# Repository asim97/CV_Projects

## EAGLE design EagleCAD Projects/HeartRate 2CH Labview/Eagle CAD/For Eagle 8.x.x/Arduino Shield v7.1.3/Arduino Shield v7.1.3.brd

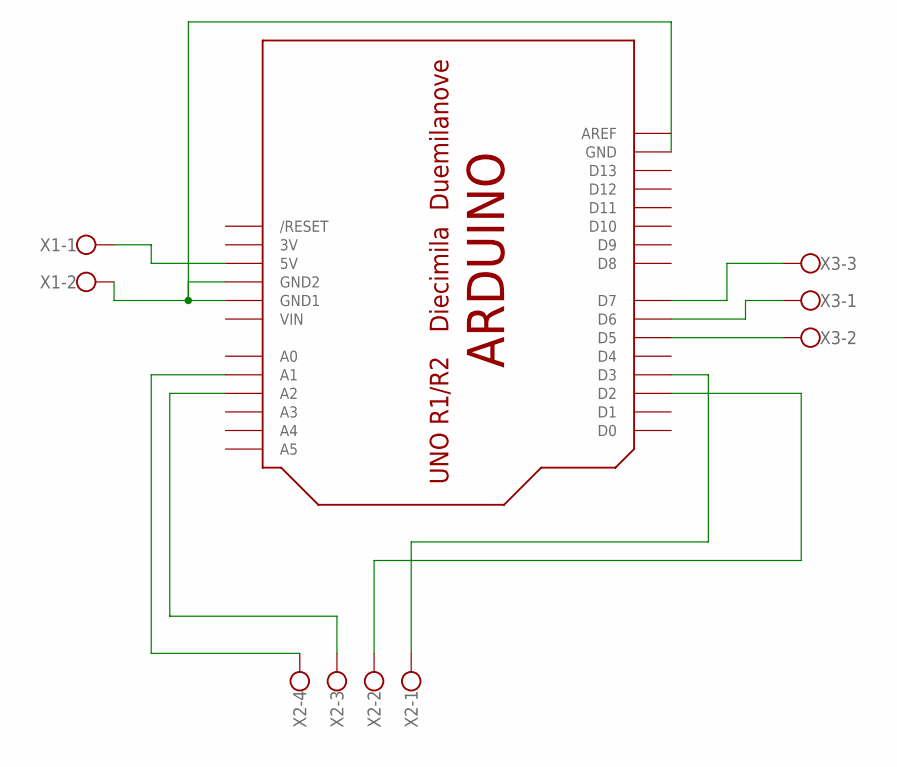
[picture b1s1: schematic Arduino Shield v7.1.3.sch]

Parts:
U$1: ARDUINOUNO; ARDUINO
X1: W237-102
X2: W237-4
X3: W237-103

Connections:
3V: U$1.3V
GND: U$1.GND, U$1.GND1, U$1.GND2, X1.2
unnamed: U$1.A1, X2.4
unnamed: U$1.A2, X2.3
unnamed: U$1.D3, X2.1
unnamed: U$1.D5, X3.2
unnamed: U$1.D6, X3.1
unnamed: U$1.D7, X3.3
unnamed: U$1.D2, X2.2
unnamed: U$1.5V, X1.1
VIN: U$1.VIN

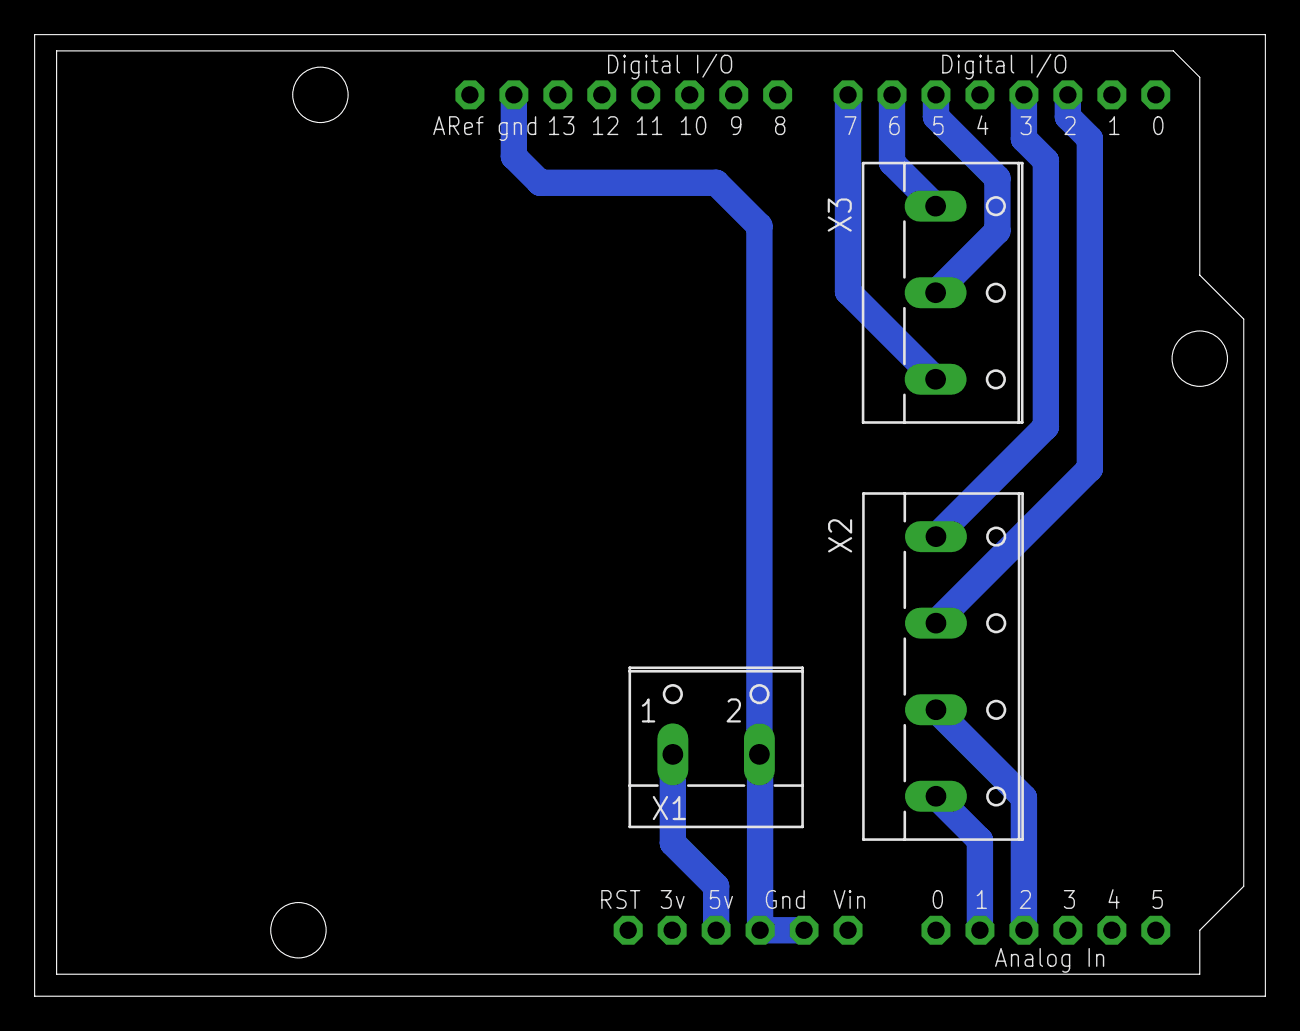
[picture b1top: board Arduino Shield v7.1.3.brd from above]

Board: 2 copper layers, 71.1 x 55.6 mm, 4 parts (0 on the bottom side), 9 nets.

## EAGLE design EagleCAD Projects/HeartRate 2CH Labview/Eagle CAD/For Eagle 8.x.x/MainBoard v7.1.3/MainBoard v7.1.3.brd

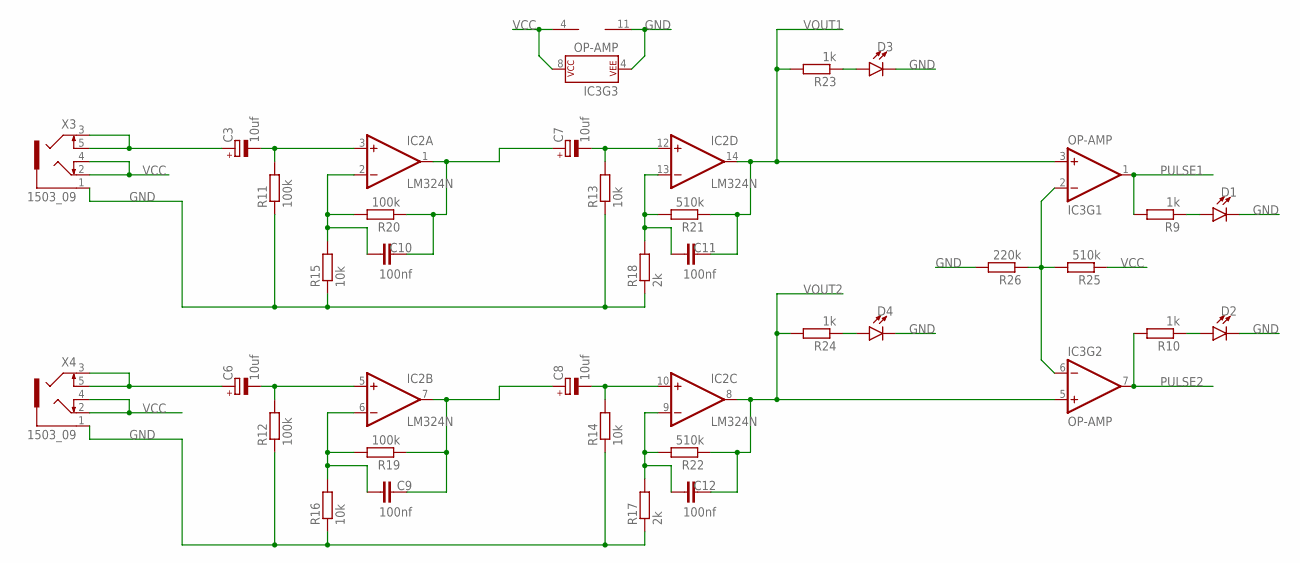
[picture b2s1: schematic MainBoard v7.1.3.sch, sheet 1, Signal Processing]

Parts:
C3, C6, C7, C8: 10uf; E2-5
C9, C10, C11, C12: 100nf; C050-030X075
D1, D2, D3, D4: LED5MM; LED_5MM
IC2: LM324N; DIL14
IC3: OP-AMP; DIP08
R9, R10, R23, R24: 1k; 0207/10
R11, R12, R19, R20: 100k; 0207/10
R13, R14, R15, R16: 10k; 0207/10
R17, R18: 2k; 0207/10
R21, R22, R25: 510k; 0207/10
R26: 220k; 0207/10
X3, X4: 1503_09

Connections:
GND: D1.K (C), D2.K (C), D3.K (C), D4.K (C), IC2.11 (V-), IC3.4 (P$V-), R11.1, R12.1, R13.1, R14.1, R15.1, R16.1, R17.1, R18.1, R26.2, X3.1, X4.1; also elsewhere on the board
unnamed: C8.+, C9.2, IC2.7 (OUT), R19.1
unnamed: C9.1, IC2.6 (-IN), R16.2, R19.2
unnamed: D1.A, R9.1
unnamed: C7.+, C10.2, IC2.1 (OUT), R20.1
unnamed: C10.1, IC2.2 (-IN), R15.2, R20.2
unnamed: C11.1, IC2.13 (-IN), R18.2, R21.2
unnamed: IC3.2 (-IN), IC3.6 (-IN), R25.2, R26.1
unnamed: C12.1, IC2.9 (-IN), R17.2, R22.2
unnamed: C6.+, X4.3, X4.5
unnamed: D2.A, R10.1
unnamed: C3.+, X3.3, X3.5
unnamed: C6.-, IC2.5 (+IN), R12.2
unnamed: C7.-, IC2.12 (+IN), R13.2
unnamed: C8.-, IC2.10 (+IN), R14.2
unnamed: C3.-, IC2.3 (+IN), R11.2
unnamed: D3.A, R23.1
unnamed: D4.A, R24.1
PULSE1: IC3.1 (OUT), R9.2; also elsewhere on the board
PULSE2: IC3.7 (OUT), R10.2; also elsewhere on the board
VCC: IC2.4 (V+), IC3.8 (P$V+), R25.1, X3.2, X3.4, X4.2, X4.4; also elsewhere on the board
VOUT1: C11.2, IC2.14 (OUT), IC3.3 (+IN), R21.1, R23.2; also elsewhere on the board
VOUT2: C12.2, IC2.8 (OUT), IC3.5 (+IN), R22.1, R24.2; also elsewhere on the board

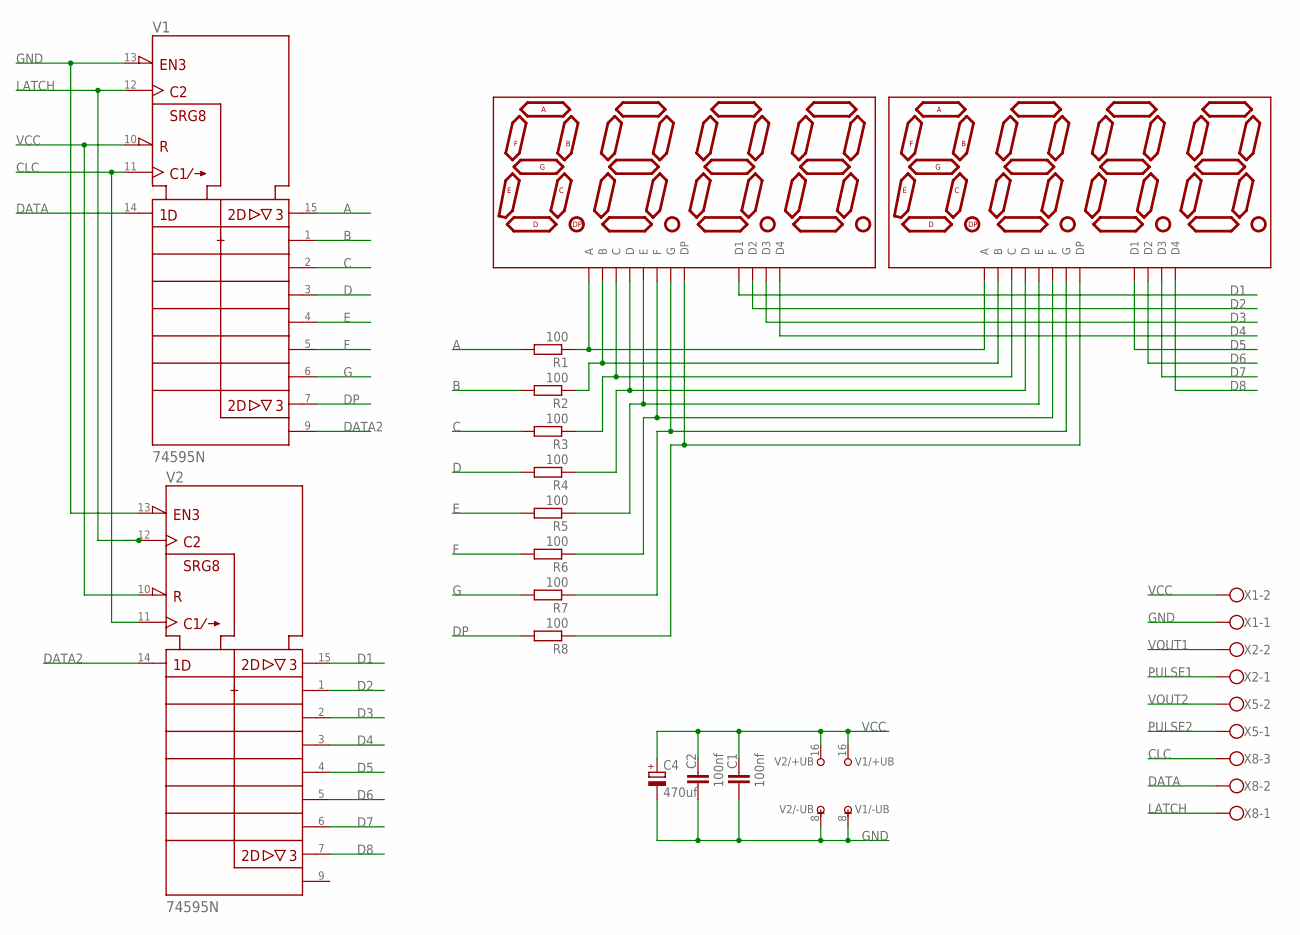
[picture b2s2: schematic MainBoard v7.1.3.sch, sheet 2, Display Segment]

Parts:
C1, C2: 100nf; C050-030X075
C4: 470uf; E3,5-8
DISP1, DISP2: ATA8041AB; 7-SEGMENT-4DIGIT-20MM
R1, R2, R3, R4, R5, R6, R7, R8: 100; 0207/10
V1, V2: 74595N; DIL16
X1, X2, X5: W237-102
X8: W237-103

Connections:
A: R1.2, V1.15 (QA)
B: R2.2, V1.1 (QB)
C: R3.2, V1.2 (QC)
CLC: V1.11 (SRCK), V2.11 (SRCK), X8.3
D: R4.2, V1.3 (QD)
D1: DISP2.12 (D1), V2.15 (QA)
D2: DISP2.9 (D2), V2.1 (QB)
D3: DISP2.8 (D3), V2.2 (QC)
D4: DISP2.6 (D4), V2.3 (QD)
D5: DISP1.12 (D1), V2.4 (QE)
D6: DISP1.9 (D2), V2.5 (QF)
D7: DISP1.8 (D3), V2.6 (QG)
D8: DISP1.6 (D4), V2.7 (QH)
DATA: V1.14 (SER), X8.2
DATA2: V1.9 (QH*), V2.14 (SER)
DP: R8.2, V1.7 (QH)
E: R5.2, V1.4 (QE)
F: R6.2, V1.5 (QF)
G: R7.2, V1.6 (QG)
GND: C1.1, C2.1, C4.-, V1.8 (-UB), V1.13 (!G), V2.8 (-UB), V2.13 (!G), X1.1; also elsewhere on the board
LATCH: V1.12 (RCK), V2.12 (RCK), X8.1
unnamed: DISP1.11 (A), DISP2.11 (A), R1.1
unnamed: DISP1.7 (B), DISP2.7 (B), R2.1
unnamed: DISP1.4 (C), DISP2.4 (C), R3.1
unnamed: DISP1.2 (D), DISP2.2 (D), R4.1
unnamed: DISP1.1 (E), DISP2.1 (E), R5.1
unnamed: DISP1.10 (F), DISP2.10 (F), R6.1
unnamed: DISP1.5 (G), DISP2.5 (G), R7.1
unnamed: DISP1.3 (DP), DISP2.3 (DP), R8.1
PULSE1: X2.1; also elsewhere on the board
PULSE2: X5.1; also elsewhere on the board
VCC: C1.2, C2.2, C4.+, V1.10 (!SRCLR), V1.16 (+UB), V2.10 (!SRCLR), V2.16 (+UB), X1.2; also elsewhere on the board
VOUT1: X2.2; also elsewhere on the board
VOUT2: X5.2; also elsewhere on the board

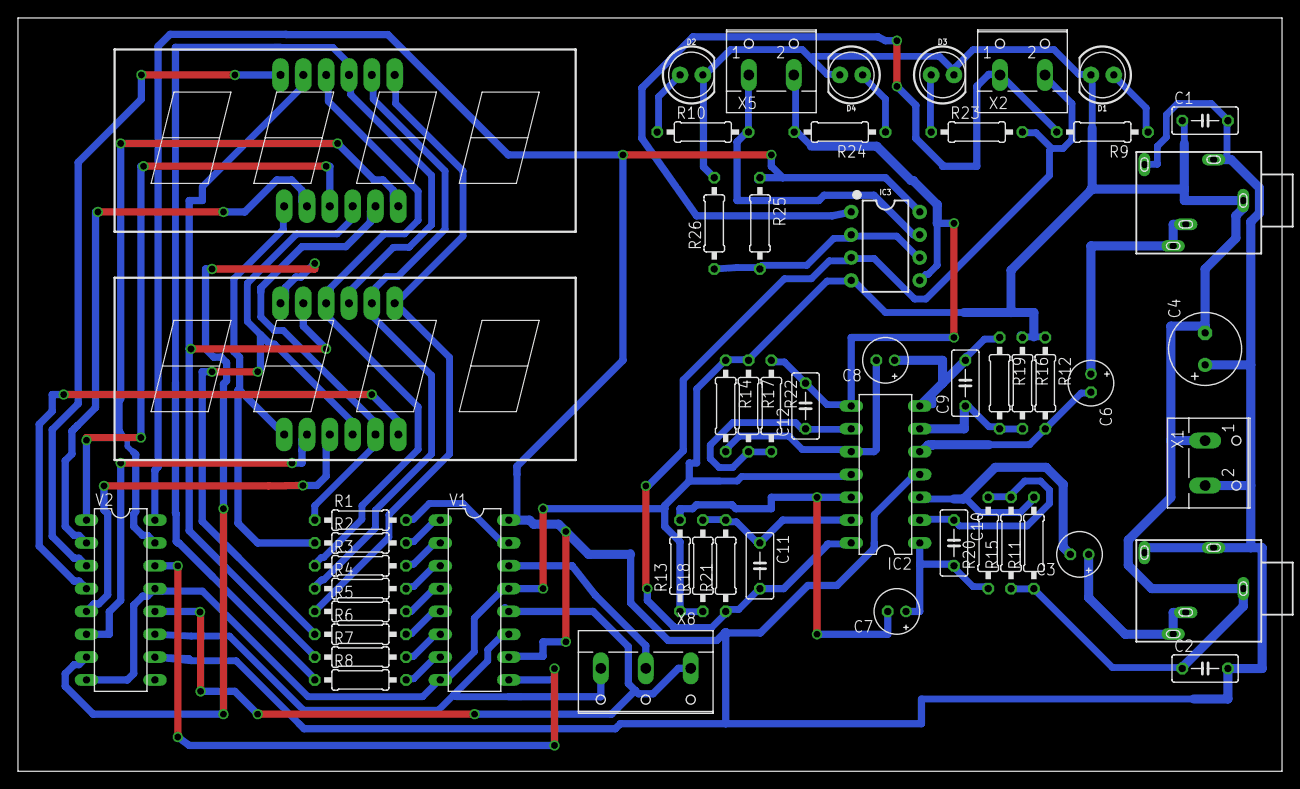
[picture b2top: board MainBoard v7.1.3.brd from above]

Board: 2 copper layers, 140.6 x 83.8 mm, 53 parts (0 on the bottom side), 51 nets.

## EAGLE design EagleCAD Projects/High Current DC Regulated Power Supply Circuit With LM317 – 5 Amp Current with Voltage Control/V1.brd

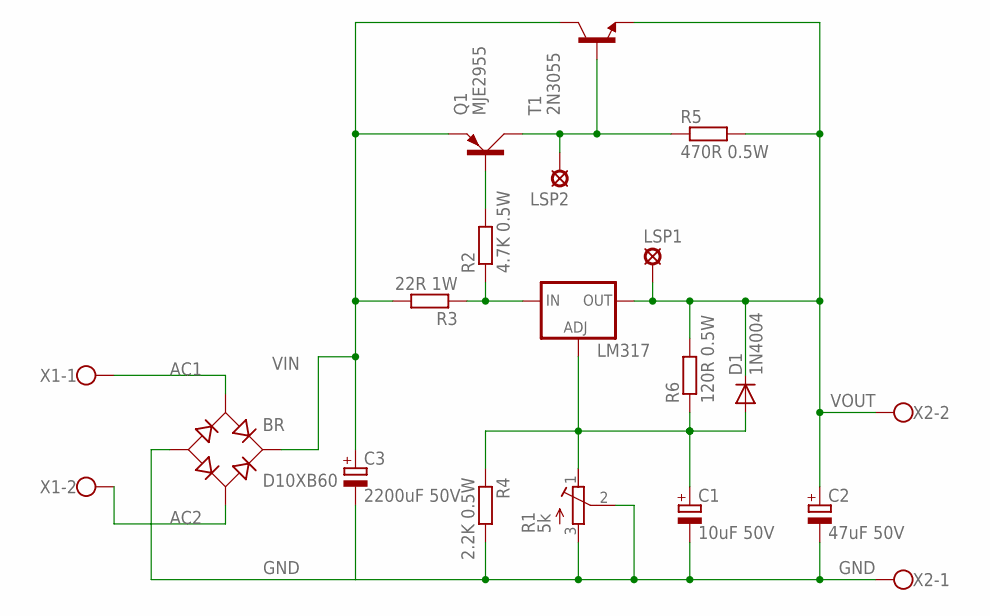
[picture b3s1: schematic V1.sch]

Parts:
BR: D10XB60; DX10B60
C1: 10uF 50V; E2,5-5
C2: 47uF 50V; E5-8,5
C3: 2200uF 50V; E7,5-18
D1: 1N4004; DO41-10
LM317: V_REG_317SINK; TO220-ADJ
LSP1, LSP2: SE13
Q1: MJE2955; TO220AV
R1: 5k; RTRIMT93XA
R2: 4.7K 0.5W; 0617/17
R3: 22R 1W; 0617/17
R4: 2.2K 0.5W; 0617/17
R5: 470R 0.5W; 0617/17
R6: 120R 0.5W; 0617/17
T1: 2N3055; TO3
X1, X2: W237-102

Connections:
AC1: BR.AC1, X1.1
AC2: BR.AC2, X1.2
GND: BR.-, C1.-, C2.-, C3.-, R1.2 (S), R1.3 (A), R4.2, X2.1
unnamed: LM317.IN, R2.1, R3.1
unnamed: Q1.B, R2.2
unnamed: LSP2.MP, Q1.C, R5.1, T1.B
unnamed: C1.+, D1.A, LM317.ADJ, R1.1 (E), R4.1, R6.1
VIN: BR.+, C3.+, Q1.E, R3.2, T1.C, T1.C/ (C)
VOUT: C2.+, D1.C, LM317.OUT, LSP1.MP, R5.2, R6.2, T1.E, X2.2

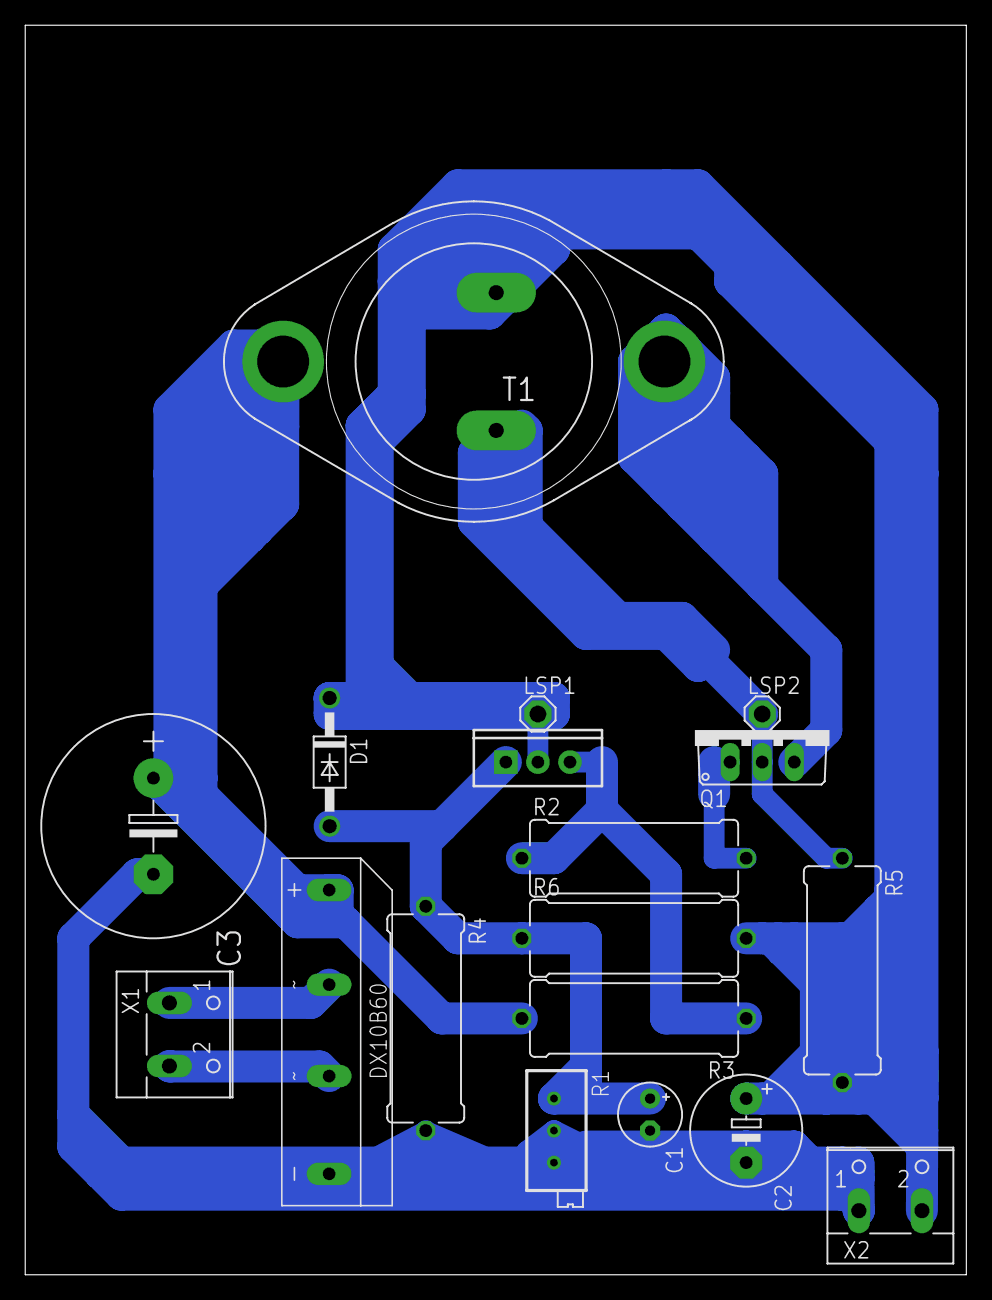
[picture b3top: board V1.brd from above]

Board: 2 copper layers, 74.6 x 99.0 mm, 18 parts (0 on the bottom side), 9 nets.

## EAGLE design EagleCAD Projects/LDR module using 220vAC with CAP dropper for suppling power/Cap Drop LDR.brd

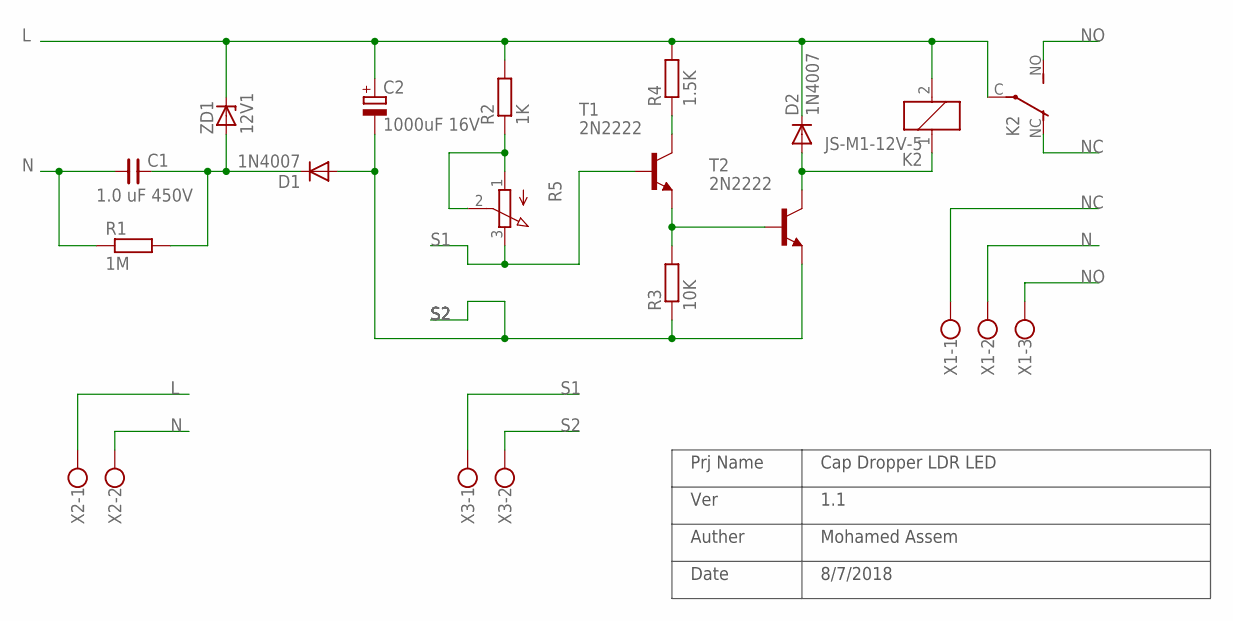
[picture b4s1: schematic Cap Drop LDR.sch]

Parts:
C1: 1.0 uF 450V; C150-190X070
C2: 1000uF 16V; E5-8,5
D1, D2: 1N4007; DO41-10
K2: JS-M1-12V-5; JS-M
R1: 1M; 0207/10
R2: 1K; 0207/10
R3: 10K; 0207/10
R4: 1.5K; 0207/10
R5: 3RP/1610N
T1, T2: 2N2222; TO92-EBC-OVAL
X1: W237-103
X2, X3: W237-102
ZD1: 12V1; DO35Z10

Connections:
L: C2.+, D2.C, K2.2, K2.C, R2.2, R4.2, X2.1, ZD1.C
N: C1.1, R1.1, X1.2, X2.2
unnamed: R3.2, T1.E, T2.B
unnamed: D2.A, K2.1, T2.C
unnamed: C1.2, D1.C, R1.2, ZD1.A
unnamed: R4.1, T1.C
unnamed: R2.1, R5.1 (A), R5.2 (S)
NC: K2.NC (O), X1.1
NO: K2.NO (S), X1.3
S1: R5.3 (E), T1.B, X3.1
S2: C2.-, D1.A, R3.1, T2.E, X3.2

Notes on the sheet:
Prj Name
Ver
Auther
Date
Cap Dropper LDR LED
Mohamed Assem
8/7/2018
1.1

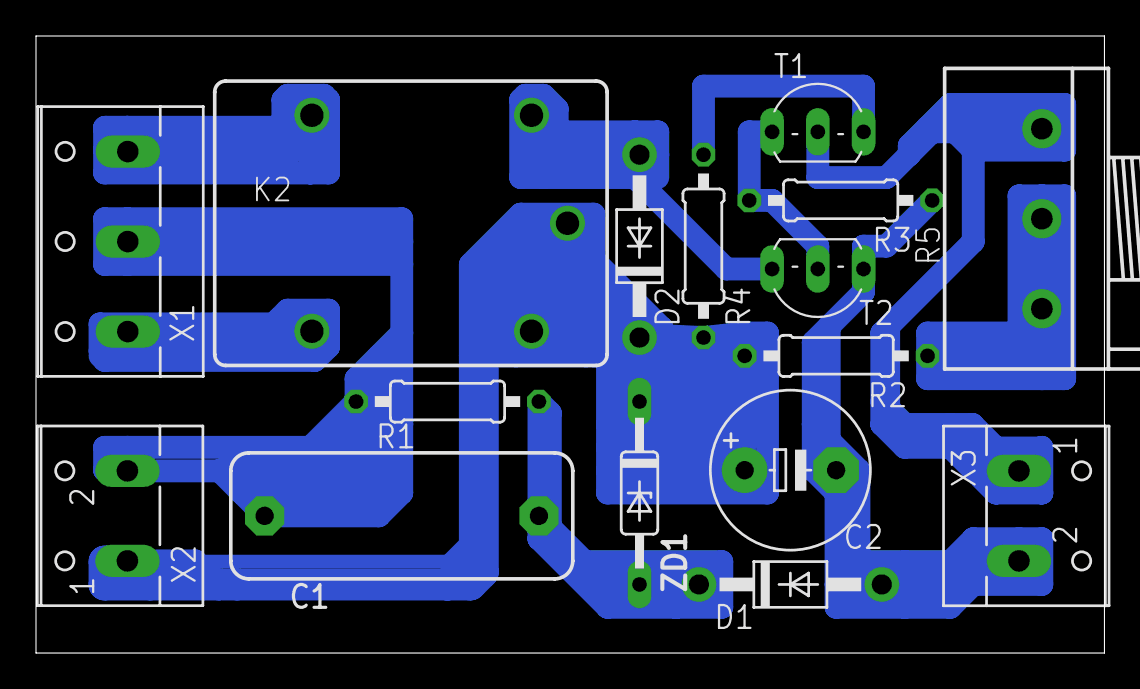
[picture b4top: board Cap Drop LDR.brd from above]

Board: 2 copper layers, 59.4 x 34.3 mm, 16 parts (0 on the bottom side), 11 nets.

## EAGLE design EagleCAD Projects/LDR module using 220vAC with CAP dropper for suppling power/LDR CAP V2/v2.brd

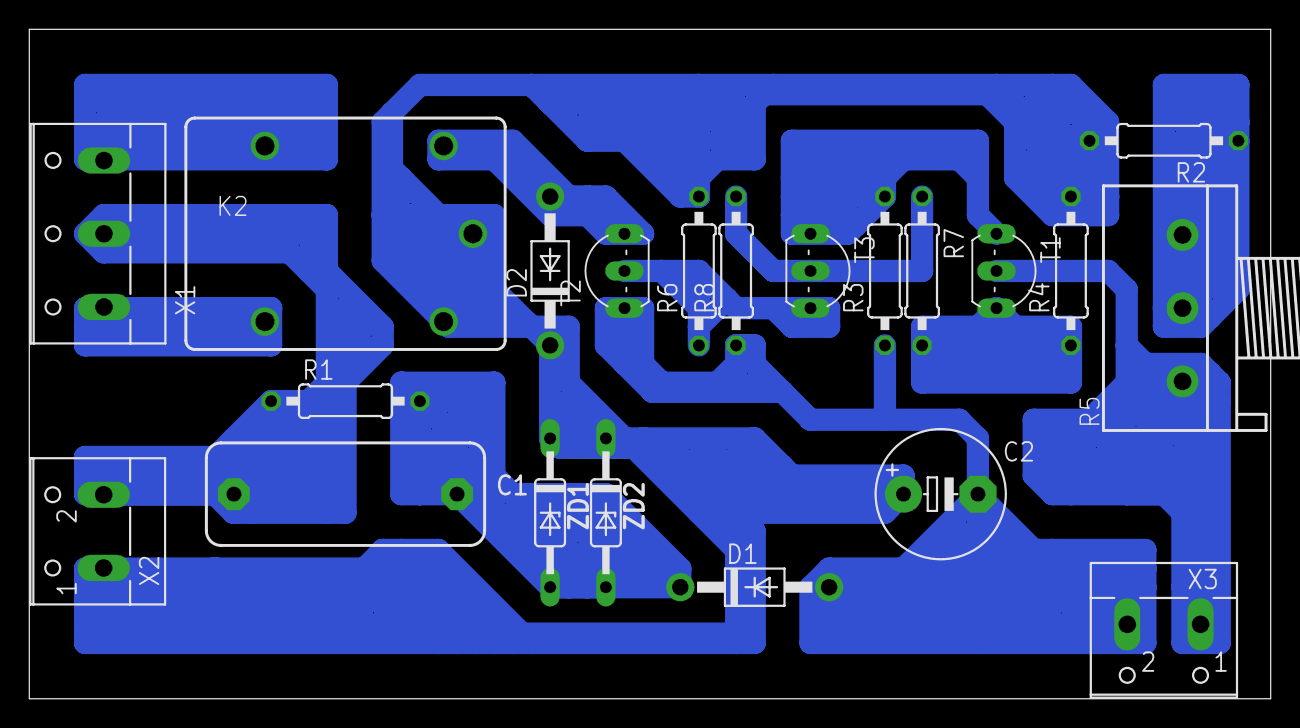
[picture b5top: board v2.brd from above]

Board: 2 copper layers, 84.8 x 45.7 mm, 21 parts (0 on the bottom side), 13 nets.

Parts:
C1: 1 uF 450V; C150-190X070
C2: 1000uF 35V; E5-8,5
D1, D2: 1N4007; DO41-10
K2: JS-M1-24V-5; JS-M
R1: 1M; 0207/10
R2, R6: 1K; 0207/10
R3: 51K; 0207/10
R4: 10K; 0207/10
R5: 100k; 3RP/1610N
R7, R8: 22K; 0207/10
T1, T2, T3: 2N2222; TO92-EBC-OVAL
X1: W237-103
X2, X3: W237-102
ZD1, ZD2: 24V 1Wat; DO35Z10

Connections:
L: C2.+, D2.C, K2.2, K2.C, R2.2, R4.2, R6.2, X2.1, ZD1.C, ZD2.C
N: C1.1, R1.1, X1.2, X2.2
unnamed: R7.1, R8.2, T3.B
unnamed: R3.2, T1.E, T3.E
unnamed: D2.A, K2.1, T2.C
unnamed: C1.2, D1.C, R1.2, ZD1.A, ZD2.A
unnamed: R4.1, R7.2, T1.C
unnamed: R6.1, T2.B, T3.C
unnamed: R2.1, R5.2, R5.3
NC: K2.NC, X1.1
NO: K2.NO, X1.3
S1: R5.1, T1.B, X3.1
S2: C2.-, D1.A, R3.1, R8.1, T2.E, X3.2

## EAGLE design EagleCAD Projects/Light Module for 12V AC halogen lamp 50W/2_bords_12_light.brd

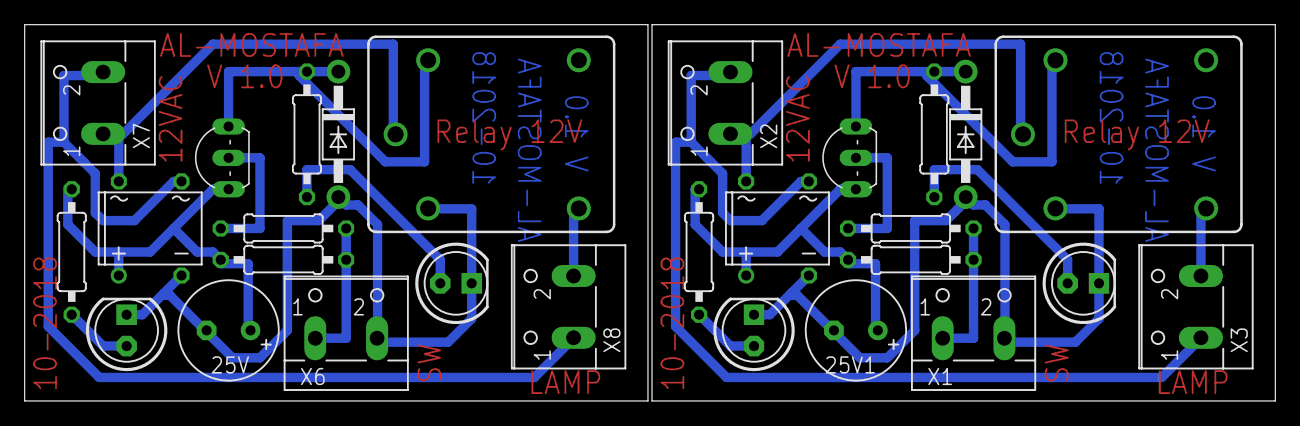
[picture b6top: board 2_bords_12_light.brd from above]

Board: 2 copper layers, 101.3 x 30.5 mm, 28 parts (0 on the bottom side), 20 nets.

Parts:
25V, 25V1: 100uF; E3,5-8
B1, B2: DBDB101G; DB
D1, D2: 1N5817; DO41-10
K1, K3: JS-M1-24V-5; JS-M
LD1, LD2, LD3, LD4: LED5MM
R1, R3: 2.2k; 0207/10
R2, R4: 10K; 0207/10
R5, R6, R7, R8: 10k; 0207/10
T1, T3: 2N5401; TO92-EBC
X1, X2, X3, X6, X7, X8: W237-102

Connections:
12VDC_IN: 25V.+, B1.+, R2.2, R7.2, T3.E
12VDC_IN1: 25V1.+, B2.+, R4.2, R8.2, T1.E
AC1-1: B2.AC2, K1.C, X2.1
AC1-12: B1.AC2, K3.C, X7.1
AC2-1: B2.AC1, X2.2, X3.1
AC2-12: B1.AC1, X7.2, X8.1
GND: 25V.-, B1.-, D1.A, K3.1, LD2.K, LD4.K, X6.2
GND1: 25V1.-, B2.-, D2.A, K1.1, LD1.K, LD3.K, X1.2
unnamed: R3.1, T1.B
unnamed: LD1.A, R5.1
unnamed: LD3.A, R8.1
unnamed: R1.1, T3.B
unnamed: LD4.A, R7.1
unnamed: LD2.A, R6.1
SUC: R1.2, R2.1, X6.1
SUC1: R3.2, R4.1, X1.1
SUC_RE: K3.NO, X8.2
SUC_RE1: K1.NO, X3.2
TR_OUT: D1.C, K3.2, R6.2, T3.C
TR_OUT1: D2.C, K1.2, R5.2, T1.C

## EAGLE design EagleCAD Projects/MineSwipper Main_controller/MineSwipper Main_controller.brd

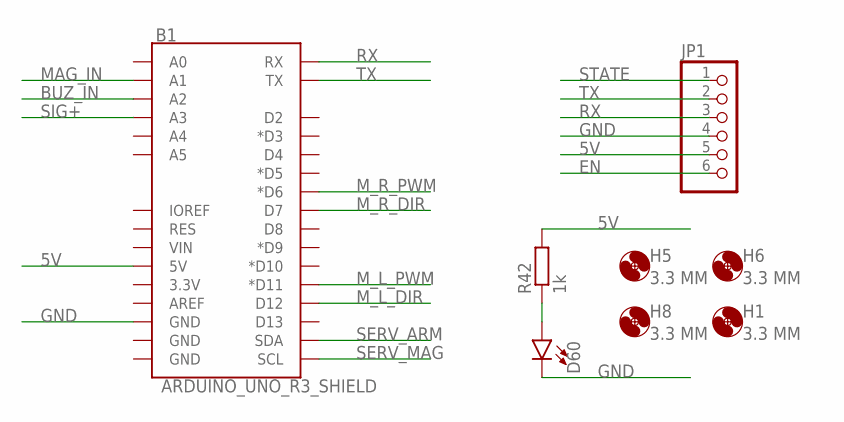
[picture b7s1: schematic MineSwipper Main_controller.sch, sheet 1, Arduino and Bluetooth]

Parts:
B1: ARDUINO_UNO_R3_SHIELD; UNO_R3_SHIELD_NOLABELS_LOCK
D60: LED5MM; LED_5MM
H1, H5, H6, H8: 3.3 MM; 3,3
JP1: PINHD-1X6; 1X06
R42: 1k; 0207/10

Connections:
5V: B1.5V, JP1.5, R42.2; also elsewhere on the board
BUZ_IN: B1.A2; also elsewhere on the board
EN: JP1.6
GND: B1.GND@2 (GND), D60.K (C), JP1.4; also elsewhere on the board
MAG_IN: B1.A1; also elsewhere on the board
M_L_DIR: B1.D12; also elsewhere on the board
M_L_PWM: B1.D11 (*D11); also elsewhere on the board
M_R_DIR: B1.D7; also elsewhere on the board
M_R_PWM: B1.D6 (*D6); also elsewhere on the board
unnamed: D60.A, R42.1
RX: B1.RX, JP1.3
SERV_ARM: B1.SDA; also elsewhere on the board
SERV_MAG: B1.SCL; also elsewhere on the board
SIG+: B1.A3; also elsewhere on the board
STATE: JP1.1
TX: B1.TX, JP1.2

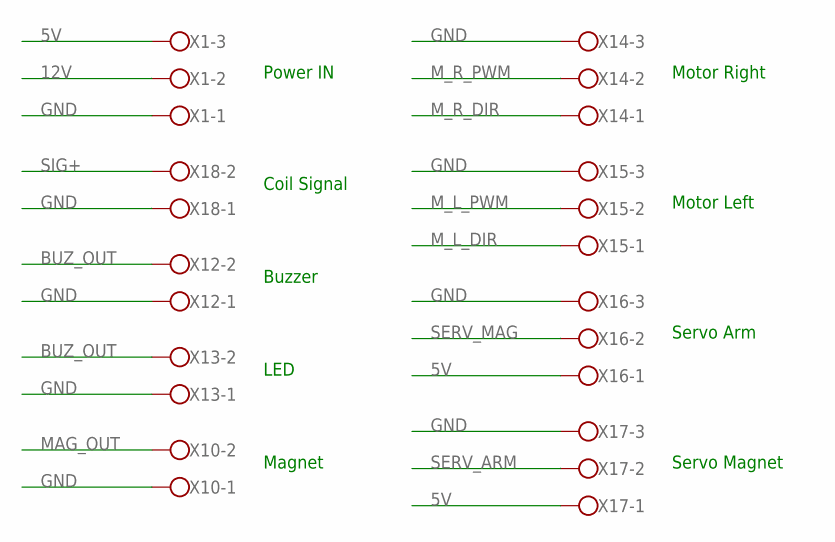
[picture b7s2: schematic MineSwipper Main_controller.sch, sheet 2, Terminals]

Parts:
X1, X14, X15, X16, X17: W237-103
X10, X12, X13, X18: W237-102

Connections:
5V: X1.3, X16.1, X17.1; also elsewhere on the board
12V: X1.2; also elsewhere on the board
BUZ_OUT: X12.2, X13.2; also elsewhere on the board
GND: X1.1, X10.1, X12.1, X13.1, X14.3, X15.3, X16.3, X17.3, X18.1; also elsewhere on the board
MAG_OUT: X10.2; also elsewhere on the board
M_L_DIR: X15.1; also elsewhere on the board
M_L_PWM: X15.2; also elsewhere on the board
M_R_DIR: X14.1; also elsewhere on the board
M_R_PWM: X14.2; also elsewhere on the board
SERV_ARM: X17.2; also elsewhere on the board
SERV_MAG: X16.2; also elsewhere on the board
SIG+: X18.2; also elsewhere on the board

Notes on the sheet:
Motor Right
Motor Left
Servo Arm
Servo Magnet
Power IN
Buzzer
LED
Magnet
Coil Signal

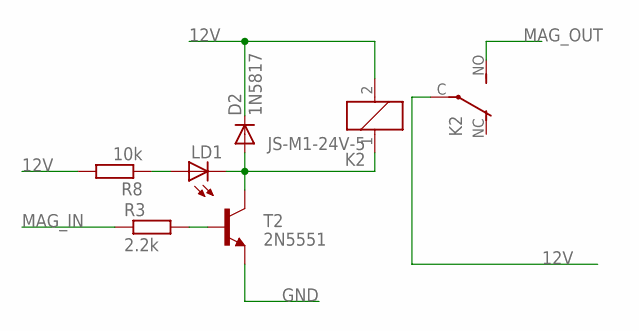
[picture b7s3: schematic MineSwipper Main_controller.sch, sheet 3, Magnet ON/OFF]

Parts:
D2: 1N5817; DO41-10
K2: JS-M1-24V-5; JS-M
LD1: LED5MM
R3: 2.2k; 0207/10
R8: 10k; 0207/10
T2: 2N5551; TO92-EBC-OVAL

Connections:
12V: D2.C, K2.2, K2.C, R8.2; also elsewhere on the board
GND: T2.E; also elsewhere on the board
MAG_IN: R3.1; also elsewhere on the board
MAG_OUT: K2.NO (S); also elsewhere on the board
unnamed: D2.A, K2.1, LD1.K (C), T2.C
unnamed: R3.2, T2.B
unnamed: LD1.A, R8.1

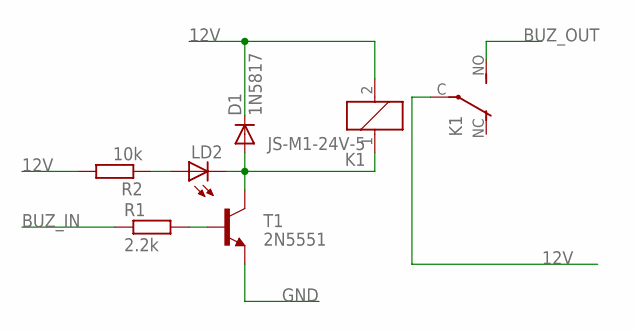
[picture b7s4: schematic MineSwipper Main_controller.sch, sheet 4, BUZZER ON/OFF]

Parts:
D1: 1N5817; DO41-10
K1: JS-M1-24V-5; JS-M
LD2: LED5MM
R1: 2.2k; 0207/10
R2: 10k; 0207/10
T1: 2N5551; TO92-EBC-OVAL

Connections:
12V: D1.C, K1.2, K1.C, R2.2; also elsewhere on the board
BUZ_IN: R1.1; also elsewhere on the board
BUZ_OUT: K1.NO (S); also elsewhere on the board
GND: T1.E; also elsewhere on the board
unnamed: D1.A, K1.1, LD2.K (C), T1.C
unnamed: R1.2, T1.B
unnamed: LD2.A, R2.1

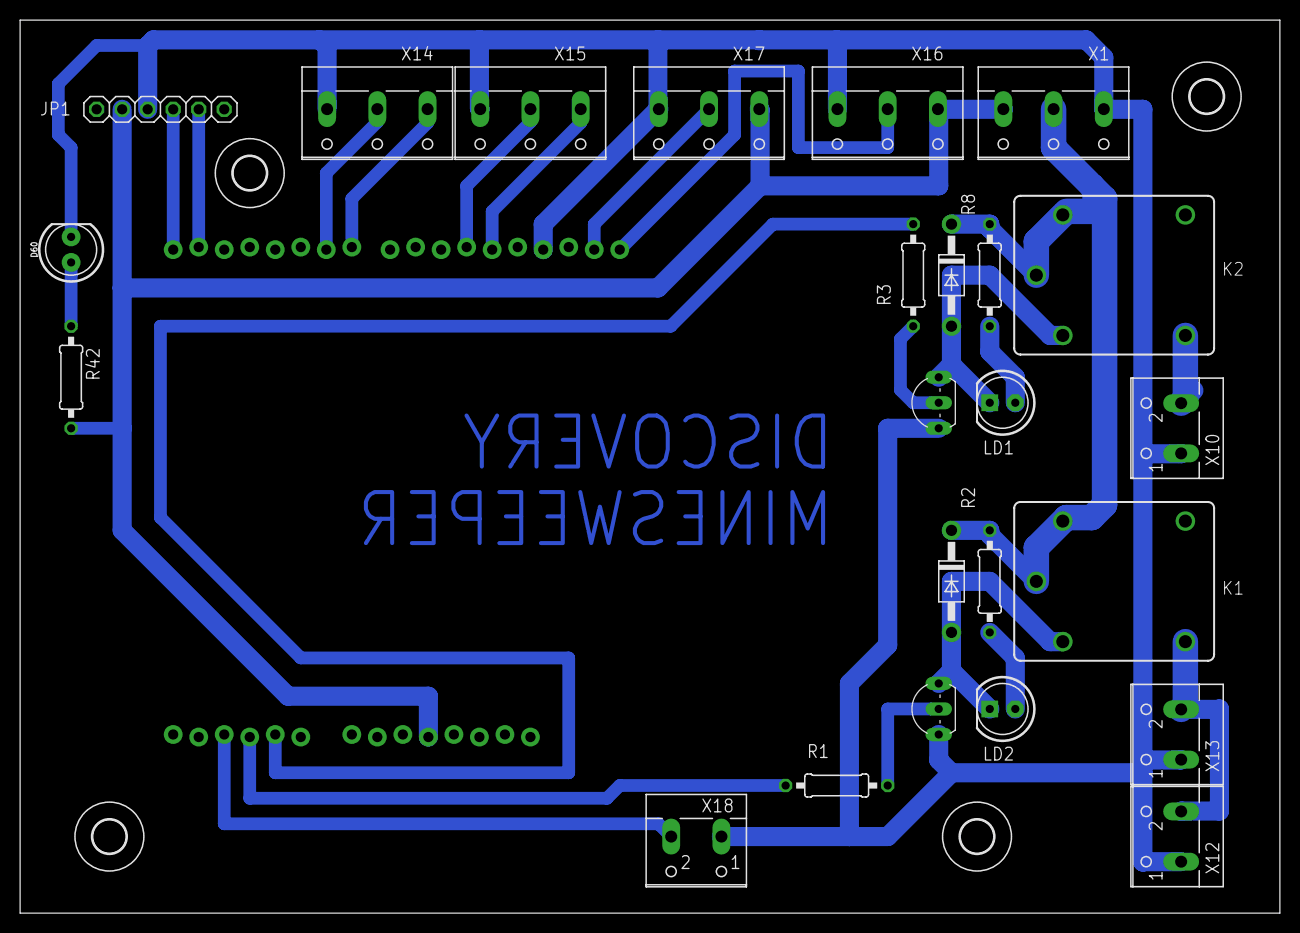
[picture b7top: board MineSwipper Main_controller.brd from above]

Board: 2 copper layers, 125.4 x 88.9 mm, 29 parts (1 on the bottom side), 23 nets.

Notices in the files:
parts and their libraries:
SparkFun-LED: Licensing: Creative Commons ShareAlike 4.0 International - https://creativecommons.org/licenses/by-sa/4.0
